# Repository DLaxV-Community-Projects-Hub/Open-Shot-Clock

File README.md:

# Open Shot Clock

Open Shot Clock is an Open Source and DIY Project aiming to minimize the barriers of entry for shot-clock-aided sports like Boxlacrosse and Sixes and maximizing the pure sports experience to an affordable price.

## Details

- 10" super bright LED digits (in color of your choice)
- indoor and outdoor usage
    - impact and water resistant portable design
    - LED brightness adjustable to your needs
- wireless and cable connection
- 12V input supply (portable battery or mains operation by AC-DC power supply)
- handheld controller
- wifi connection to smartphone
    - control option
    - settings change
    - firmware updates
- external horn for each display
- tripod stands ~2 meter height
- tested under competition conditions

The price tag is around 1000€ for materials and accessories. Depending on which design and battery options you choose, it might cost more.

For more information have a look at our [wiki](https://github.com/DLaxV-Community-Projects-Hub/Open-Shot-Clock/wiki/Open-Shot-Clock-Wiki) or this [blog](https://devdrik.de/blog/) made by [@devdrik](https://github.com/devdrik).

## The Open Shot Clock in Action

To see the Open Shot Clock in action check out the following recordings of Lacrosse high lights in Germany:

- [Men´s European Box Lacrosse Championship 2022 - Final: England vs. Germany](https://sportdeutschland.tv/germanylacrosse/european-box-lacrosse-championship-final-england-vs-germany) (face off at 0:07:20)
- [Women´s German Indoor Championchip 2023 - Final: HLC Rot-Weiss München vs. HTHC Hamburg A](https://sportdeutschland.tv/germanylacrosse/deutsche-indoor-lacrosse-meisterschaft-2023-finale) (draw at 0:07:35)
- [Men´s German Box Lacrosse Championchip 2023- Final: SG Süd vs. SC Frankfurt 1880](https://sportdeutschland.tv/germanylacrosse/deutsche-box-lacrosse-meisterschaft-2023-finale) (face off at 0:10:15)
- [Women´s German Indoor Championchip 2022 - Final: HLC Rot-Weiss München vs. HTHC Hamburg A](https://sportdeutschland.tv/germanylacrosse/finale-lacrosse-damen-indoor-meisterschaft-2022) (draw at 0:09:20)
- [Men´s German Box Lacrosse Championchip 2022- Final: Spreewölfe Berlin vs. KKHT SW Köln](https://sportdeutschland.tv/germanylacrosse/deutsche-meisterschaften-box-lacrosse-2022-spreewoelfe-berlin-vs-kkht-sw-koeln) (starting at Part 2)

## What´s Included Here

- Design Documentation for Open Shot Clock Displays and Controller
    - CAD and PCB designs
    - 3d printing files
    - DIY Building Instructions Manual (german)
    - BOM for Displays, Controller and accessories (german)
    - User Manual (german)
    - Source Code to run Displays and Controller
- Project Wiki (work in progress)

## Usage

To build your own Open Shot Clock you can find all documents/information in the [documentation](documentation/) folder.

### Getting All the Parts Needed

Please go through the BOM to make sure you have all parts needed available. In the BOM we have included recommendation links, where we recently purchased the parts. Be aware that you can choose from different design features which you have to cover in your purchases. The developement is stil ongoing so some design features are not yet tested or even sufficiently developed.

In the design 3d printing is requried. Make sure you print the necessary parts before starting to build or let them print by a printing service. Make sure the parts are printed with a heat and impact resistant 3d printing material. You can find recommended materials in the BOM.

For the PCBs you can use the design files to order them at a PCB manufacturer like [PCBWay](https://www.pcbway.com/) or you can get in touch with us, there are still some prototyping PCBs left of the current version. In the near future the PCB design has to be adapted to the new Heltec Lora 32 version 3.0. For now the new version is supported through a workaround. For more information check this [blog artical](https://devdrik.de/open-shot-clock-hannover/) from [@devdrik](https://github.com/devdrik).

### List of Optional Design Features:

- Displays - 19 mm thick highly machined base plate or 8 mm thick easy to build base plate
  - 19 mm makes a more stable design and is tested well
  - 8 mm base plate is much easier to build with less special machinery, but it´s not tested yet (there might be clashes with electronic parts inside the case)

- Displays - Temperature Managment (up to now we don´t know if a temperature management is necessary, to find out we integrated a temp sensor socket on the display pcbs, tests are still in planning)

  - No Cooling
  - Fan grids on the back for passiv cooling (default)
  - Active Fan with fan grids on the back (fan can be installed behind one fan grid and operated by one mosfet output, this feature is not yet included in the sourc code)

- Displays - Batteries (you can find different battery options in the BOM from which you can choose)
- Accessories - you can find different accessory options in the BOM from which you can choose
- Displays - Type-Plate customization (for having your own type-plate text you can get in touch with us, we can change the text for you)
- to be continued

### Assembling

When you have all parts available please follow the DIY Building Instructions Manual for assembling your Open Shot Clocks. Some parts like the base-, front- and back-plates or the aliminium extursion profiles need to be modified before they can be assembled. You can do the needed modification by using the drawings of these parts or you can get in touch with us, there are still some back plates left in our stock. In this [youtube playlist](https://www.youtube.com/watch?v=pQqHoa6__Ms&list=PLql27Iz3RF6tFwROZiCufJEf_9jadfyL8) you can see videos of [@devdrik](https://github.com/devdrik) performing the assembing process of an Open Shot Clock. In the future the playlist will be extended to cover all parts of the assembling process.

#### Heltec WiFi LoRa V2/V3

The V2 module is hard to get at the moment, so we added support for the new V3 version of the module, that is easy to source. To use V3 with PCBs designed for V2, you need to rewire some connections. So make sure not to use a V3 on a V2 PCB without modification!

What to do to use a V3 on a Display PCB v0.2:
- Do not connect GPIO21 and GPIO48 of the V3 to the display PCB
- Connect GPIO38 to the display PCB where GPIO21 would be
- Connect GPIO39 to the display PCB where GPIO48 would be
- In [config.h](code/display/include/config.h) set ```DISPLAY_PCB_VERSION V0_2_HACK```

What to do to use a V3 on a PCB for V2 (controller):
- Button BUTTON_PIN_B can not be used anymore
- Add pull-ups to all buttons (to be tested)

##### 5V Hack

Some Mosfet modules do not work with 3.3V on gate. To fix this on a v0.2 shotclock display PCB, we can disconnect the 3V3 pins from the of the heltec module and connect the corresponding pins on the display PCB to 5V of the heltec module.
This will bring all 3V3 on the display PCB to 5V, so be careful if you use a temperature sensor!

### How to Set Up the Firmware

You can find the source code for the controller and the displays in the code folder. Please just copy this repo to your VS Code with Plaformio extension and open both as projects. Fill in your preferred wifi credentials for setting up local device wifi networks to change settings. It is recommended to use different credentials for the controller and the displays to make sure you access the right devices settings.
Make sure to select the environment that fits the board you are using.

- flash controller
  - SPIFFS
  - source code
- flash displays
  - source code

## What´s Left to Do

- Tackle issues
- Build up Wiki with design insights, project history and roadmap
- Source code refactoring
- Design and test mdf display case as cost reduction opportunity
- pcb design to be ported to another open source platform and integration of heltc lora 32 v3.0 support
- Support first builders and gather feedback
- Offer english version of documents (if sufficiently demanded)
- to be continued

## How to Contribute

Feel free to customize your Open Shot Clock to your needs. For this purpose you can find the design files in the cad and pcb folders and the source code in the code folder. If you have ideas how to improve the Open Shot Clock and you need support for the integration or you want to share the benefits with the community please get in touch with us.

## Acknowledgement

Many thanks to [Ulf](https://github.com/ulf) for some initial inspiration in the approach to develop a LED shot clock. If you are looking out for a minimal and cheap setup for small indoor fields without obstacles have a look to [Ulf´s basketball shot clock tutotial](http://shotclock.de/)! With minor changes to the app it is possible to start with 30 seconds on the clock for lacrosse instead of 24 as for basketball. 

## Authors

- [@ChangeD20](https://github.com/ChangeD20)
- [@devdrik](https://github.com/devdrik)

## Contact

github@dlaxv.de

## License

[CERN OHL v2 Permissive](https://choosealicense.com/licenses/cern-ohl-p-2.0/)

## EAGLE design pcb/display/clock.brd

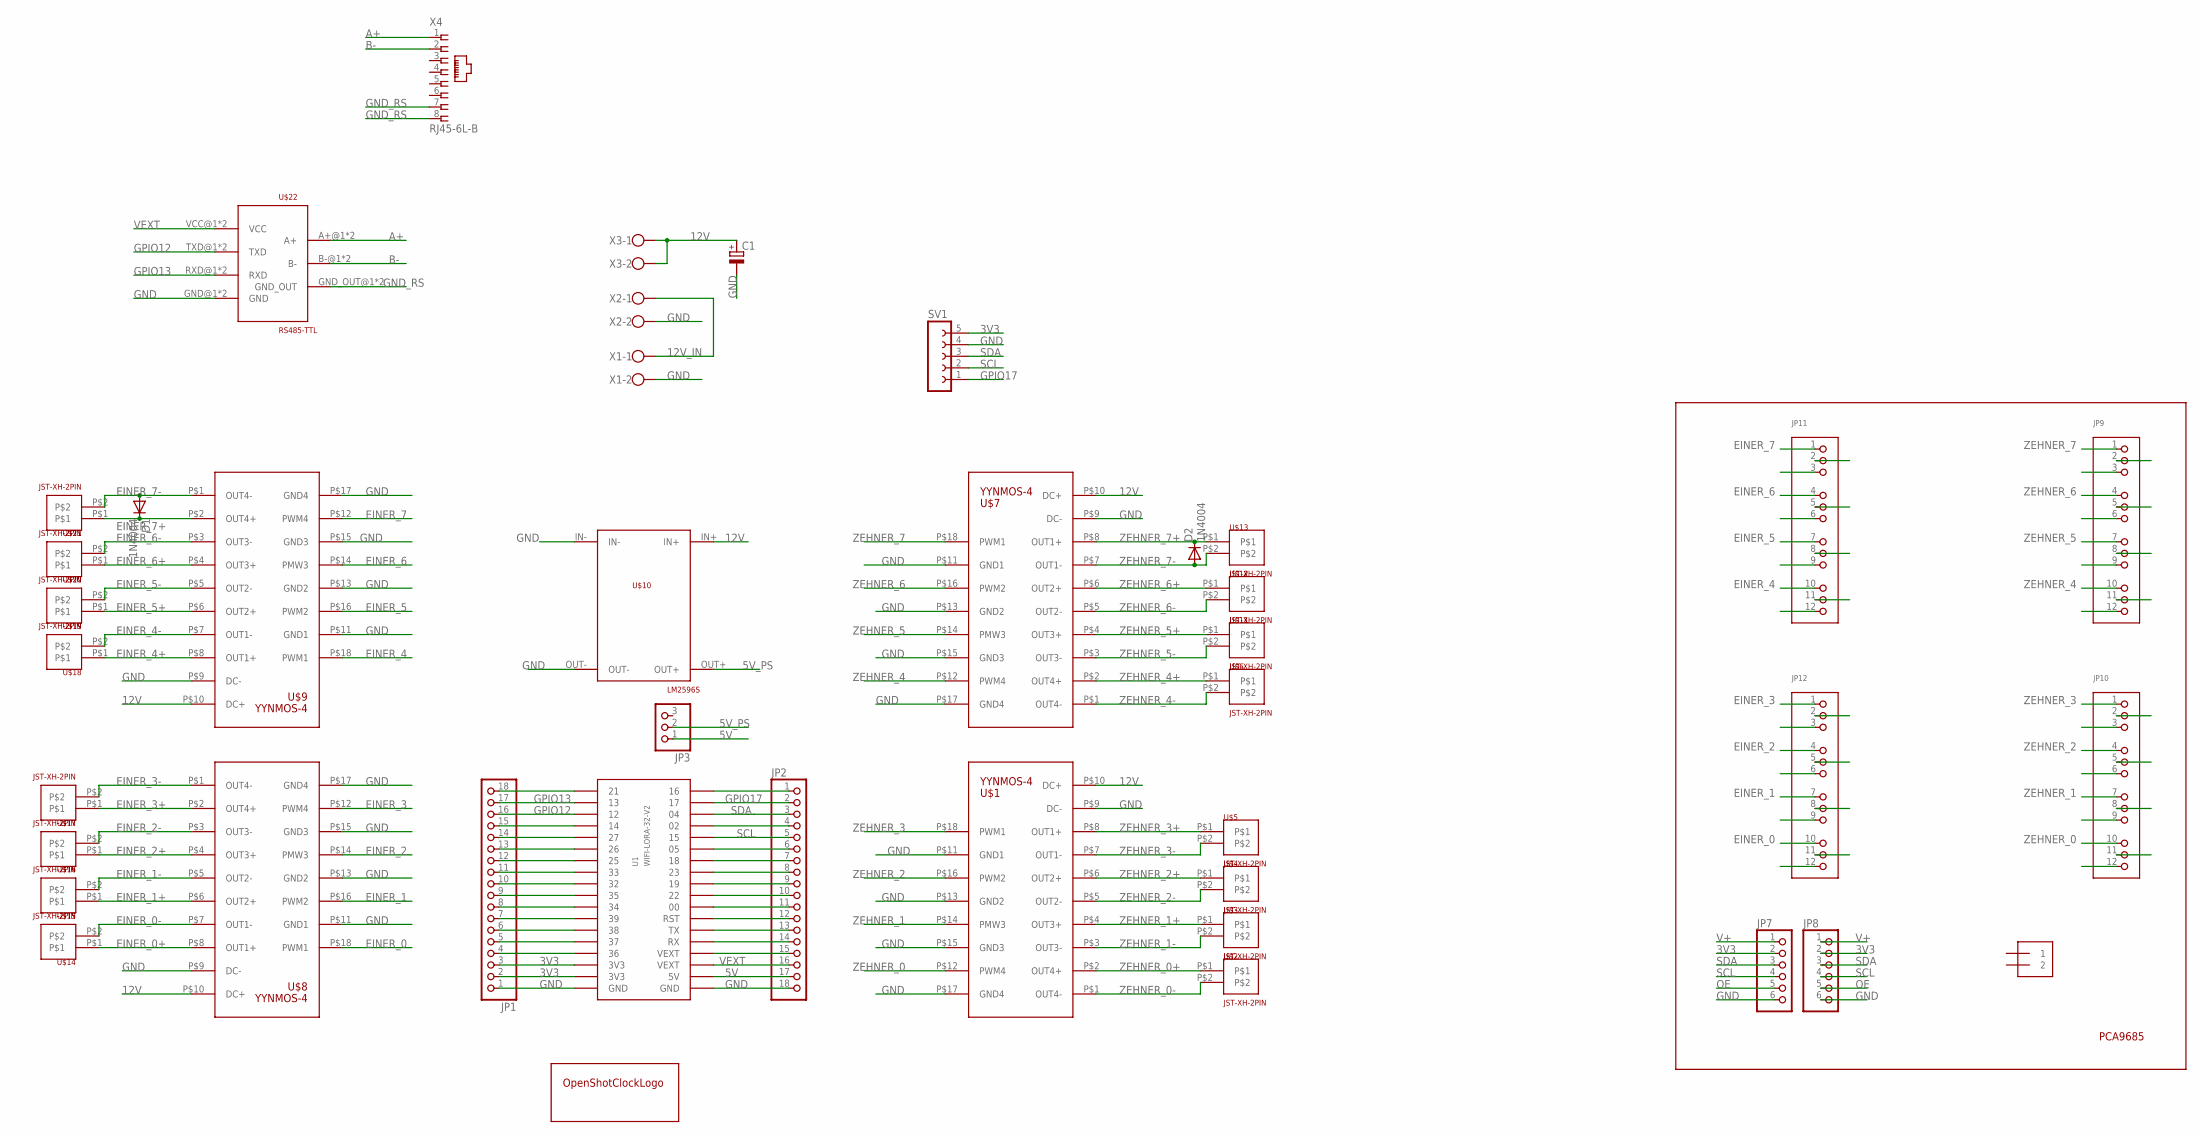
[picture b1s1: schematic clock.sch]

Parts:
C1: CPOL-EUE2.5-6; E2,5-6
D1, D2: 1N4004; DO41-10
J2: TERMBLOCK_1X2-3.5MM; 1X2-3.5MM
JP1, JP2: PINHD-1X18; 1X18
JP3: PINHD-1X3; 1X03
JP7, JP8: PINHD-1X6CB; 1X06-CLEANBIG
JP9, JP10, JP11, JP12: HEADER-3X04; 3X04
SV1: FE05-1
U1: WIFI-LORA-32-V2; 2.54MM_2X18
U$1, U$7, U$8, U$9: YYNMOS-4
U$2, U$3, U$4, U$5, U$6, U$11, U$12, U$13, U$14, U$15, U$16, U$17, U$18, U$19, U$20, U$21: JST-XH-2PIN
U$10: LM2596S
U$22: RS485-TTL
U$23: OPEN-SHOT-CLOCK-LOGO
X1, X2, X3: W237-102
X4: RJ45-6L-B; RJ45-NO-SHIELD

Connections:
3V3: JP1.2, JP1.3, JP7.2, JP8.2, SV1.5, U1.P$34 (3V3), U1.P$35 (3V3)
5V: JP2.17, JP3.1, U1.P$2 (5V)
5V_PS: JP3.2, U$10.OUT+
12V: C1.+, U$1.P$10 (DC+), U$7.P$10 (DC+), U$8.P$10 (DC+), U$9.P$10 (DC+), U$10.IN+, X3.1, X3.2
12V_IN: X1.1, X2.1
A+: U$22.A+@1 (A+), U$22.A+@2 (A+), X4.1
B-: U$22.B-@1 (B-), U$22.B-@2 (B-), X4.2
EINER_0: JP12.10, U$8.P$18 (PWM1)
EINER_0+: U$8.P$8 (OUT1+), U$14.P$1
EINER_0-: U$8.P$7 (OUT1-), U$14.P$2
EINER_1: JP12.7, U$8.P$16 (PWM2)
EINER_1+: U$8.P$6 (OUT2+), U$15.P$1
EINER_1-: U$8.P$5 (OUT2-), U$15.P$2
EINER_2: JP12.4, U$8.P$14 (PMW3)
EINER_2+: U$8.P$4 (OUT3+), U$16.P$1
EINER_2-: U$8.P$3 (OUT3-), U$16.P$2
EINER_3: JP12.1, U$8.P$12 (PWM4)
EINER_3+: U$8.P$2 (OUT4+), U$17.P$1
EINER_3-: U$8.P$1 (OUT4-), U$17.P$2
EINER_4: JP11.10, U$9.P$18 (PWM1)
EINER_4+: U$9.P$8 (OUT1+), U$18.P$1
EINER_4-: U$9.P$7 (OUT1-), U$18.P$2
EINER_5: JP11.7, U$9.P$16 (PWM2)
EINER_5+: U$9.P$6 (OUT2+), U$19.P$1
EINER_5-: U$9.P$5 (OUT2-), U$19.P$2
EINER_6: JP11.4, U$9.P$14 (PMW3)
EINER_6+: U$9.P$4 (OUT3+), U$20.P$1
EINER_6-: U$9.P$3 (OUT3-), U$20.P$2
EINER_7: JP11.1, U$9.P$12 (PWM4)
EINER_7+: D1.C, U$9.P$2 (OUT4+), U$21.P$1
EINER_7-: D1.A, U$9.P$1 (OUT4-), U$21.P$2
GND: C1.-, JP1.1, JP2.18, JP7.6, JP8.6, SV1.4, U1.P$1 (GND), U1.P$36 (GND), U$1.P$9 (DC-), U$1.P$11 (GND1), U$1.P$13 (GND2), U$1.P$15 (GND3), U$1.P$17 (GND4), U$7.P$9 (DC-), U$7.P$11 (GND1), U$7.P$13 (GND2), U$7.P$15 (GND3), U$7.P$17 (GND4), U$8.P$9 (DC-), U$8.P$11 (GND1), U$8.P$13 (GND2), U$8.P$15 (GND3), U$8.P$17 (GND4), U$9.P$9 (DC-), U$9.P$11 (GND1), U$9.P$13 (GND2), U$9.P$15 (GND3), U$9.P$17 (GND4), U$10.IN-, U$10.OUT-, U$22.GND@1 (GND), U$22.GND@2 (GND), X1.2, X2.2
GND_RS: U$22.GND_OUT@1 (GND_OUT), U$22.GND_OUT@2 (GND_OUT), X4.7, X4.8
GPIO12: JP1.16, U1.P$21 (12), U$22.TXD@1 (TXD), U$22.TXD@2 (TXD)
GPIO13: JP1.17, U1.P$20 (13), U$22.RXD@1 (RXD), U$22.RXD@2 (RXD)
GPIO17: JP2.2, SV1.1, U1.P$17 (17)
unnamed: JP1.18, U1.P$19 (21)
unnamed: JP1.15, U1.P$22 (14)
unnamed: JP1.14, U1.P$23 (27)
unnamed: JP1.13, U1.P$24 (26)
unnamed: JP1.12, U1.P$25 (25)
unnamed: JP1.11, U1.P$26 (33)
unnamed: JP1.10, U1.P$27 (32)
unnamed: JP1.9, U1.P$28 (35)
unnamed: JP1.8, U1.P$29 (34)
unnamed: JP1.7, U1.P$30 (39)
unnamed: JP1.6, U1.P$31 (38)
unnamed: JP1.5, U1.P$32 (37)
unnamed: JP1.4, U1.P$33 (36)
unnamed: JP2.1, U1.P$18 (16)
unnamed: JP2.4, U1.P$15 (02)
unnamed: JP2.6, U1.P$13 (05)
unnamed: JP2.7, U1.P$12 (18)
unnamed: JP2.8, U1.P$11 (23)
unnamed: JP2.9, U1.P$10 (19)
unnamed: JP2.10, U1.P$9 (22)
unnamed: JP2.11, U1.P$8 (00)
unnamed: JP2.12, U1.P$7 (RST)
unnamed: JP2.13, U1.P$6 (TX)
unnamed: JP2.14, U1.P$5 (RX)
unnamed: JP2.15, U1.P$4 (VEXT)
OE: JP7.5, JP8.5
SCL: JP2.5, JP7.4, JP8.4, SV1.2, U1.P$14 (15)
SDA: JP2.3, JP7.3, JP8.3, SV1.3, U1.P$16 (04)
V+: JP7.1, JP8.1
VEXT: JP2.16, U1.P$3 (VEXT), U$22.VCC@1 (VCC), U$22.VCC@2 (VCC)
ZEHNER_0: JP10.10, U$1.P$12 (PWM4)
ZEHNER_0+: U$1.P$2 (OUT4+), U$2.P$1
ZEHNER_0-: U$1.P$1 (OUT4-), U$2.P$2
ZEHNER_1: JP10.7, U$1.P$14 (PMW3)
ZEHNER_1+: U$1.P$4 (OUT3+), U$3.P$1
ZEHNER_1-: U$1.P$3 (OUT3-), U$3.P$2
ZEHNER_2: JP10.4, U$1.P$16 (PWM2)
ZEHNER_2+: U$1.P$6 (OUT2+), U$4.P$1
ZEHNER_2-: U$1.P$5 (OUT2-), U$4.P$2
ZEHNER_3: JP10.1, U$1.P$18 (PWM1)
ZEHNER_3+: U$1.P$8 (OUT1+), U$5.P$1
ZEHNER_3-: U$1.P$7 (OUT1-), U$5.P$2
ZEHNER_4: JP9.10, U$7.P$12 (PWM4)
ZEHNER_4+: U$6.P$1, U$7.P$2 (OUT4+)
ZEHNER_4-: U$6.P$2, U$7.P$1 (OUT4-)
ZEHNER_5: JP9.7, U$7.P$14 (PMW3)
ZEHNER_5+: U$7.P$4 (OUT3+), U$11.P$1
ZEHNER_5-: U$7.P$3 (OUT3-), U$11.P$2
ZEHNER_6: JP9.4, U$7.P$16 (PWM2)
ZEHNER_6+: U$7.P$6 (OUT2+), U$12.P$1
ZEHNER_6-: U$7.P$5 (OUT2-), U$12.P$2
ZEHNER_7: JP9.1, U$7.P$18 (PWM1)
ZEHNER_7+: D2.C, U$7.P$8 (OUT1+), U$13.P$1
ZEHNER_7-: D2.A, U$7.P$7 (OUT1-), U$13.P$2

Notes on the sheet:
PCA9685

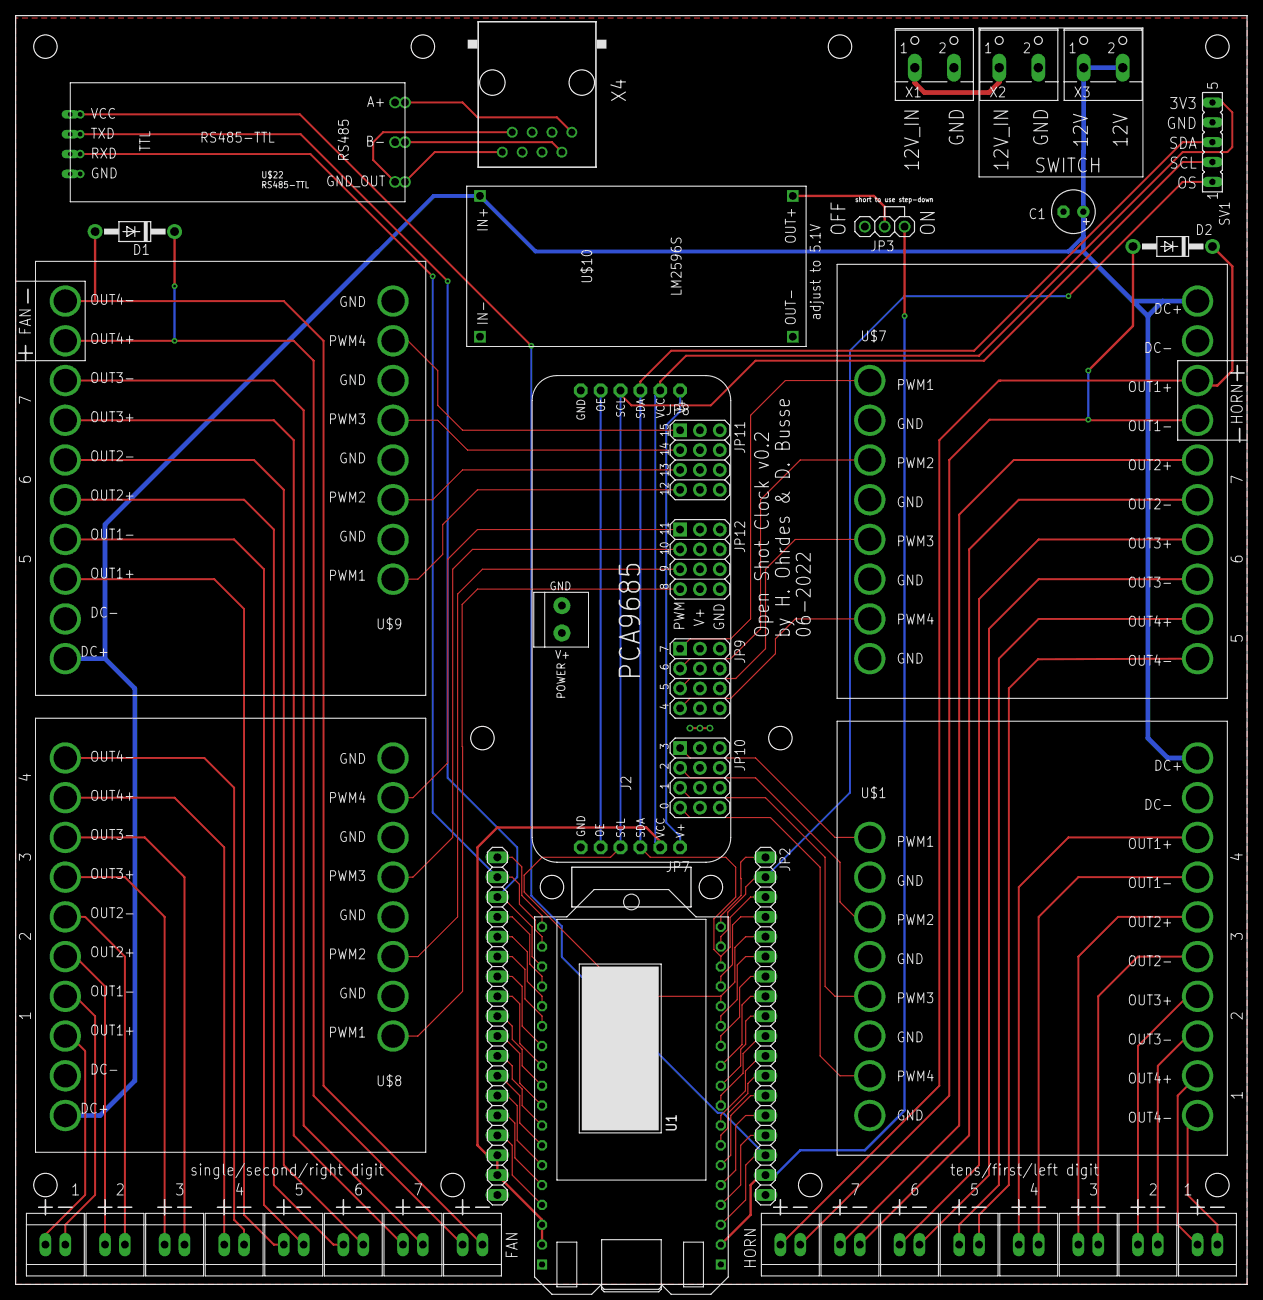
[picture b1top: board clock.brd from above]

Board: 2 copper layers, 157.5 x 162.2 mm, 42 parts (1 on the bottom side), 90 nets.

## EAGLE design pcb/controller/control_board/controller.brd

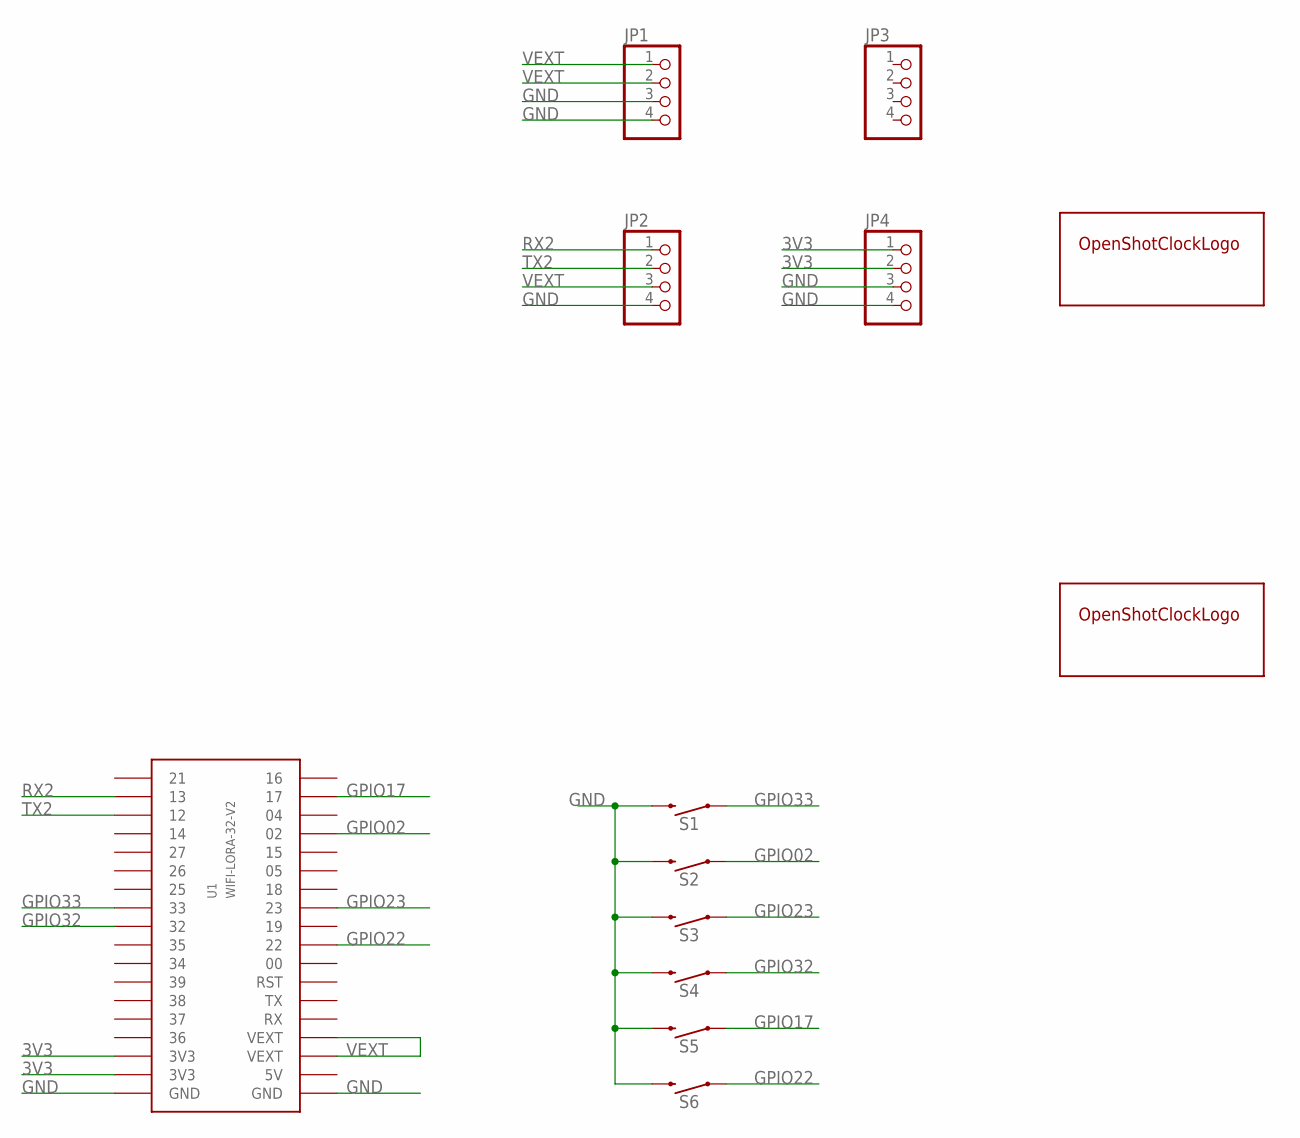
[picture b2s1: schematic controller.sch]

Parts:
JP1, JP2, JP3, JP4: PINHD-1X4; 1X04
S1, S2, S3, S4, S5, S6: MOMENTARY-SWITCH-SPST-SMD-6.0X3.5MM; TACTILE_SWITCH_SMD_6.0X3.5MM
U1: WIFI-LORA-32-V2; 2.54MM_2X18
U$2, U$5: OPEN-SHOT-CLOCK-LOGOOSCL-SMALL; OPEN-SHOT-CLOCK-LOGO-SMALL

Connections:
3V3: JP4.1, JP4.2, U1.P$34 (3V3), U1.P$35 (3V3)
GND: JP1.3, JP1.4, JP2.4, JP4.3, JP4.4, S1.2, S2.2, S3.2, S4.2, S5.2, S6.2, U1.P$1 (GND), U1.P$36 (GND)
GPIO02: S2.1, U1.P$15 (02)
GPIO17: S5.1, U1.P$17 (17)
GPIO22: S6.1, U1.P$9 (22)
GPIO23: S3.1, U1.P$11 (23)
GPIO32: S4.1, U1.P$27 (32)
GPIO33: S1.1, U1.P$26 (33)
RX2: JP2.1, U1.P$20 (13)
TX2: JP2.2, U1.P$21 (12)
VEXT: JP1.1, JP1.2, JP2.3, U1.P$3 (VEXT), U1.P$4 (VEXT)

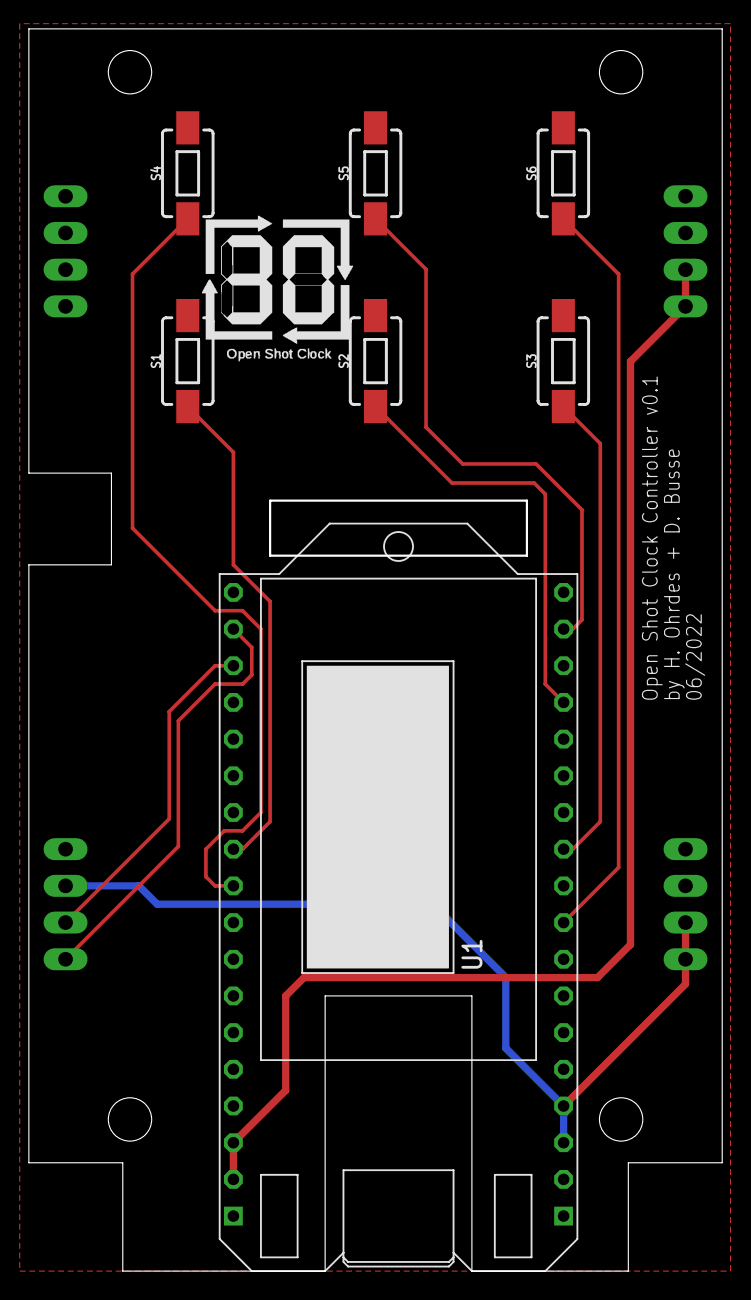
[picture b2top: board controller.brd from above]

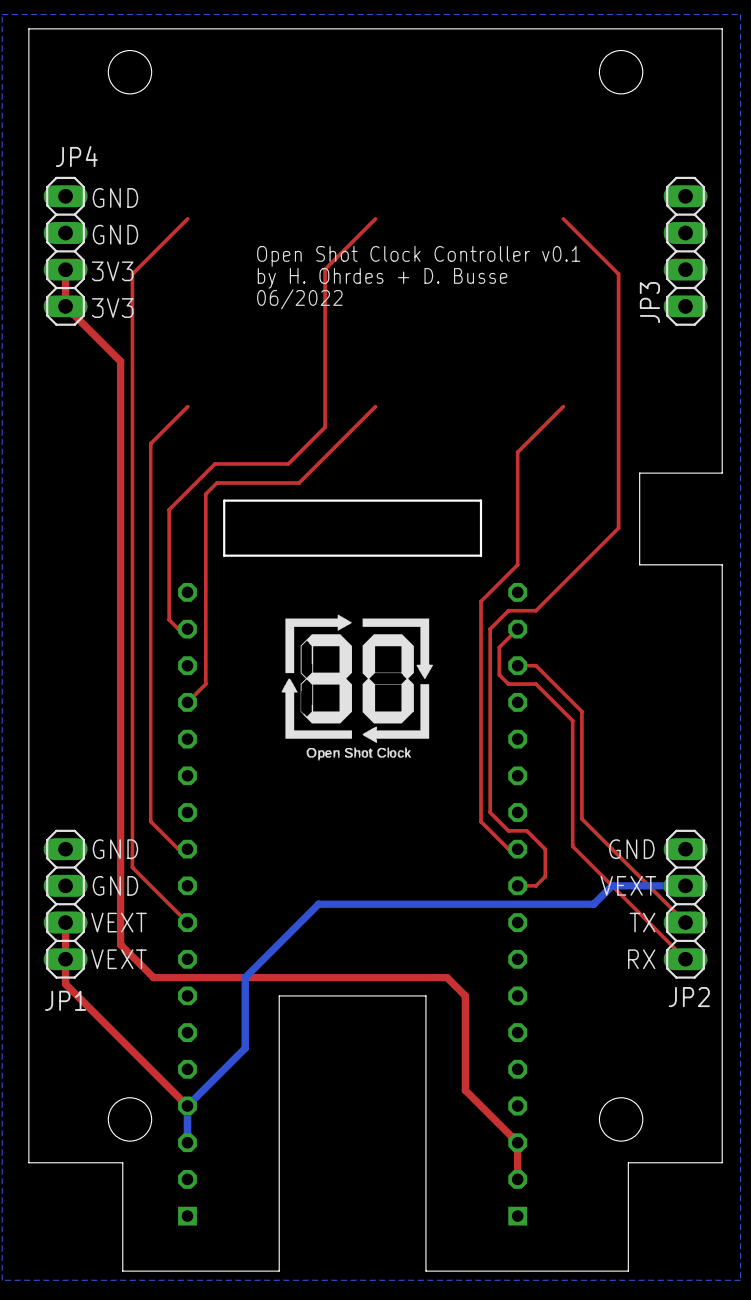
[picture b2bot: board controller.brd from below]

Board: 2 copper layers, 48.0 x 86.0 mm, 13 parts (5 on the bottom side), 11 nets.

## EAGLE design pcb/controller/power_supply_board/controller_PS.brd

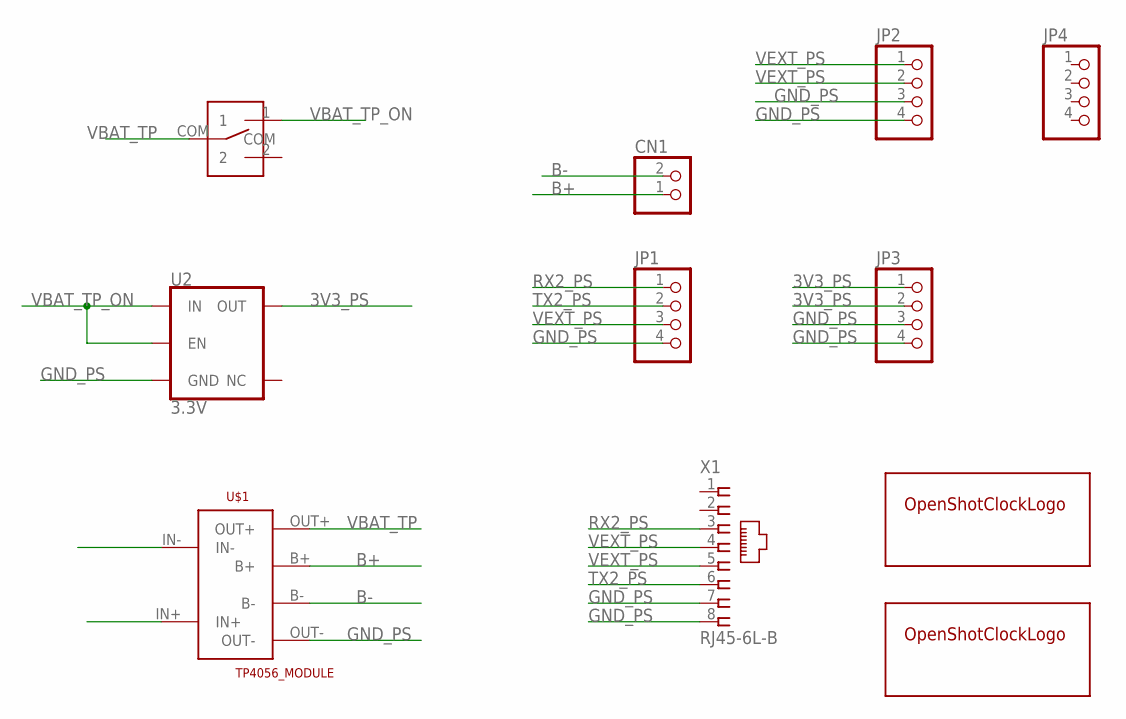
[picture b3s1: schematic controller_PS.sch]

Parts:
CN1: JST_2PIN-THM-RA; JST-PH-2-THM-RA
JP1, JP2, JP3, JP4: PINHD-1X4; 1X04
U2: 3.3V; SOT23-5
U$1: TP4056_MODULE
U$3, U$4: OPEN-SHOT-CLOCK-LOGOOSCL-SMALL; OPEN-SHOT-CLOCK-LOGO-SMALL
U$6: SK12D07VG4
X1: RJ45-6L-B; RJ45-NO-SHIELD

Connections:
3V3_PS: JP3.1, JP3.2, U2.5 (OUT)
B+: CN1.1 (2), U$1.B+
B-: CN1.2 (1), U$1.B-
GND_PS: JP1.4, JP2.3, JP2.4, JP3.3, JP3.4, U2.2 (GND), U$1.OUT-, X1.7, X1.8
RX2_PS: JP1.1, X1.3
TX2_PS: JP1.2, X1.6
VBAT_TP: U$1.OUT+, U$6.COM
VBAT_TP_ON: U2.1 (IN), U2.3 (EN), U$6.1
VEXT_PS: JP1.3, JP2.1, JP2.2, X1.4, X1.5

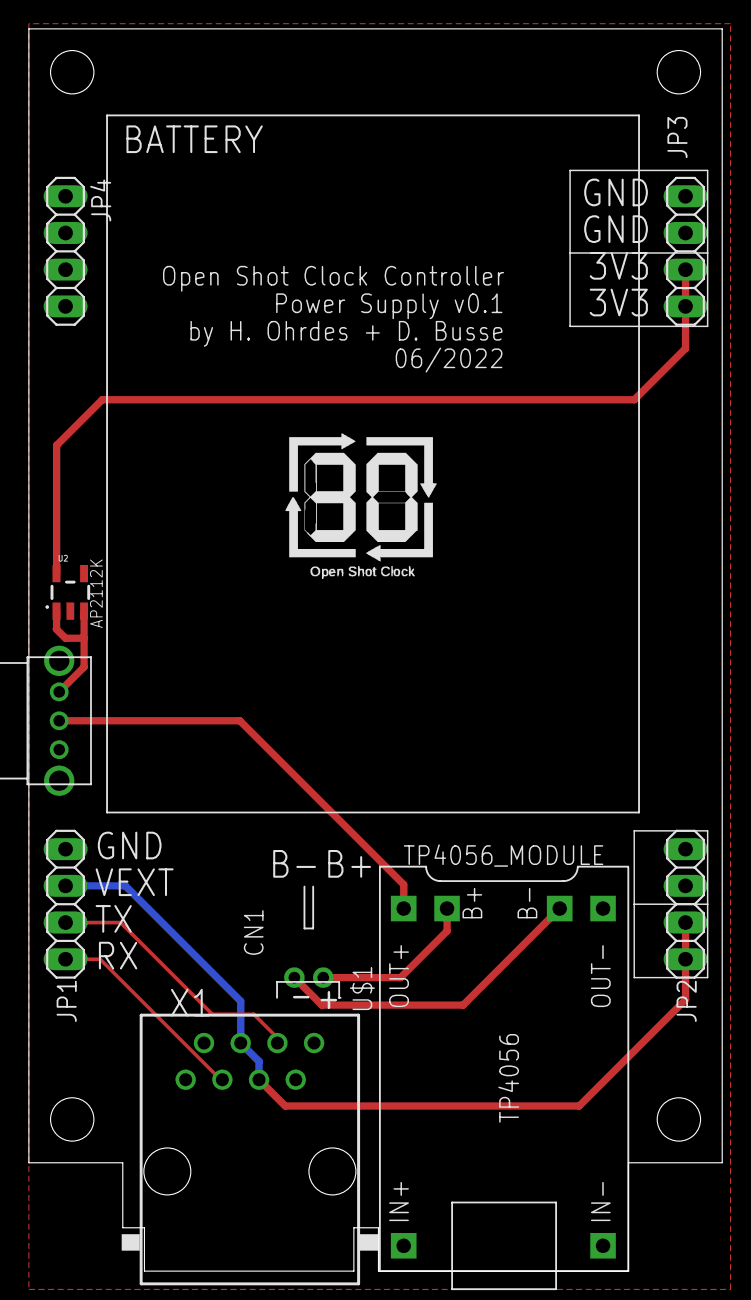
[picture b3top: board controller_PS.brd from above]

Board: 2 copper layers, 48.0 x 86.0 mm, 11 parts (1 on the bottom side), 9 nets.

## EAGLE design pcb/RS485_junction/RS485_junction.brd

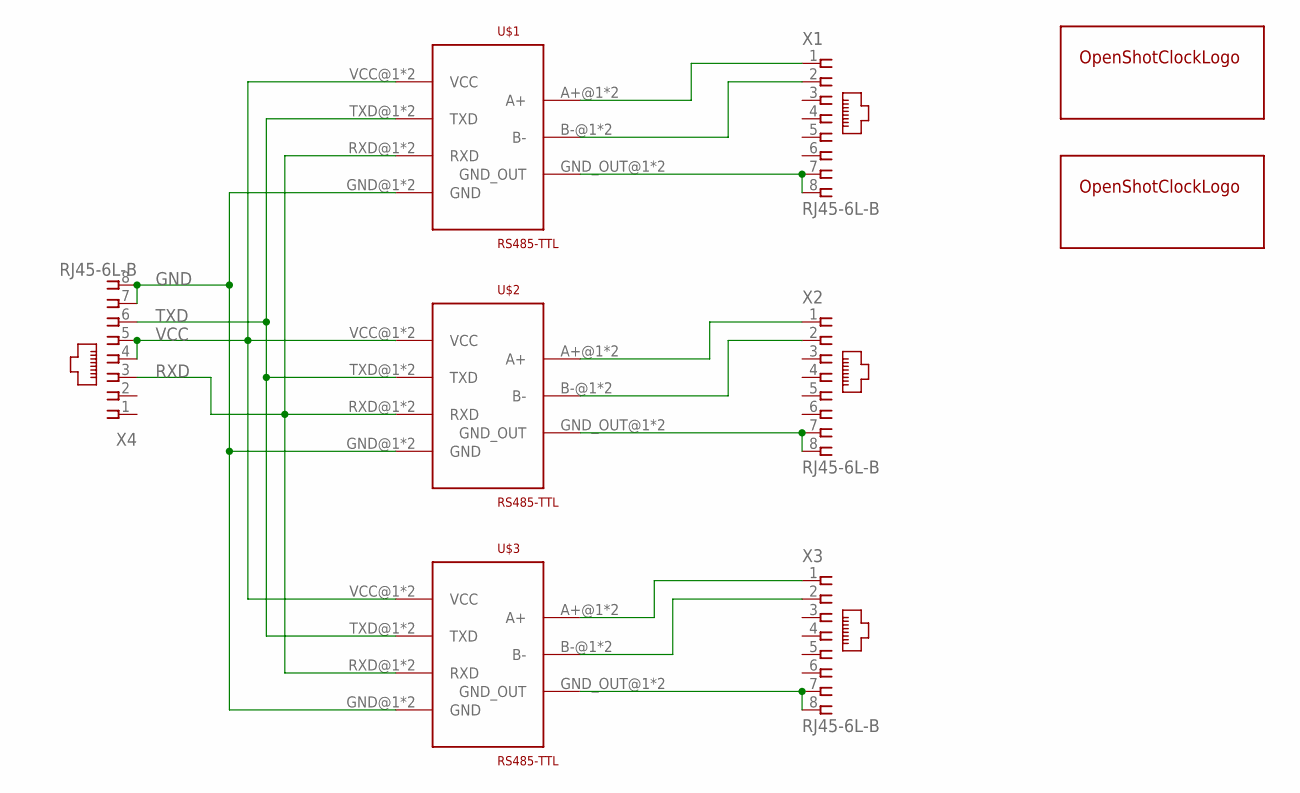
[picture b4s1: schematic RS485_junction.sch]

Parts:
U$1, U$2, U$3: RS485-TTL
U$4: OPEN-SHOT-CLOCK-LOGOOSCL-SMALL; OPEN-SHOT-CLOCK-LOGO-SMALL
U$5: OPEN-SHOT-CLOCK-LOGOOSCL-H50MM; OPEN-SHOT-CLOCK-LOGO-H50MM
X1, X2, X3, X4: RJ45-6L-B; RJ45-NO-SHIELD

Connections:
GND: U$1.GND@1 (GND), U$1.GND@2 (GND), U$2.GND@1 (GND), U$2.GND@2 (GND), U$3.GND@1 (GND), U$3.GND@2 (GND), X4.7, X4.8
unnamed: U$1.A+@1 (A+), U$1.A+@2 (A+), X1.1
unnamed: U$1.B-@1 (B-), U$1.B-@2 (B-), X1.2
unnamed: U$1.GND_OUT@1 (GND_OUT), U$1.GND_OUT@2 (GND_OUT), X1.7, X1.8
unnamed: U$2.A+@1 (A+), U$2.A+@2 (A+), X2.1
unnamed: U$2.B-@1 (B-), U$2.B-@2 (B-), X2.2
unnamed: U$2.GND_OUT@1 (GND_OUT), U$2.GND_OUT@2 (GND_OUT), X2.7, X2.8
unnamed: U$3.GND_OUT@1 (GND_OUT), U$3.GND_OUT@2 (GND_OUT), X3.7, X3.8
unnamed: U$3.A+@1 (A+), U$3.A+@2 (A+), X3.1
unnamed: U$3.B-@1 (B-), U$3.B-@2 (B-), X3.2
RXD: U$1.RXD@1 (RXD), U$1.RXD@2 (RXD), U$2.RXD@1 (RXD), U$2.RXD@2 (RXD), U$3.RXD@1 (RXD), U$3.RXD@2 (RXD), X4.3
TXD: U$1.TXD@1 (TXD), U$1.TXD@2 (TXD), U$2.TXD@1 (TXD), U$2.TXD@2 (TXD), U$3.TXD@1 (TXD), U$3.TXD@2 (TXD), X4.6
VCC: U$1.VCC@1 (VCC), U$1.VCC@2 (VCC), U$2.VCC@1 (VCC), U$2.VCC@2 (VCC), U$3.VCC@1 (VCC), U$3.VCC@2 (VCC), X4.4, X4.5

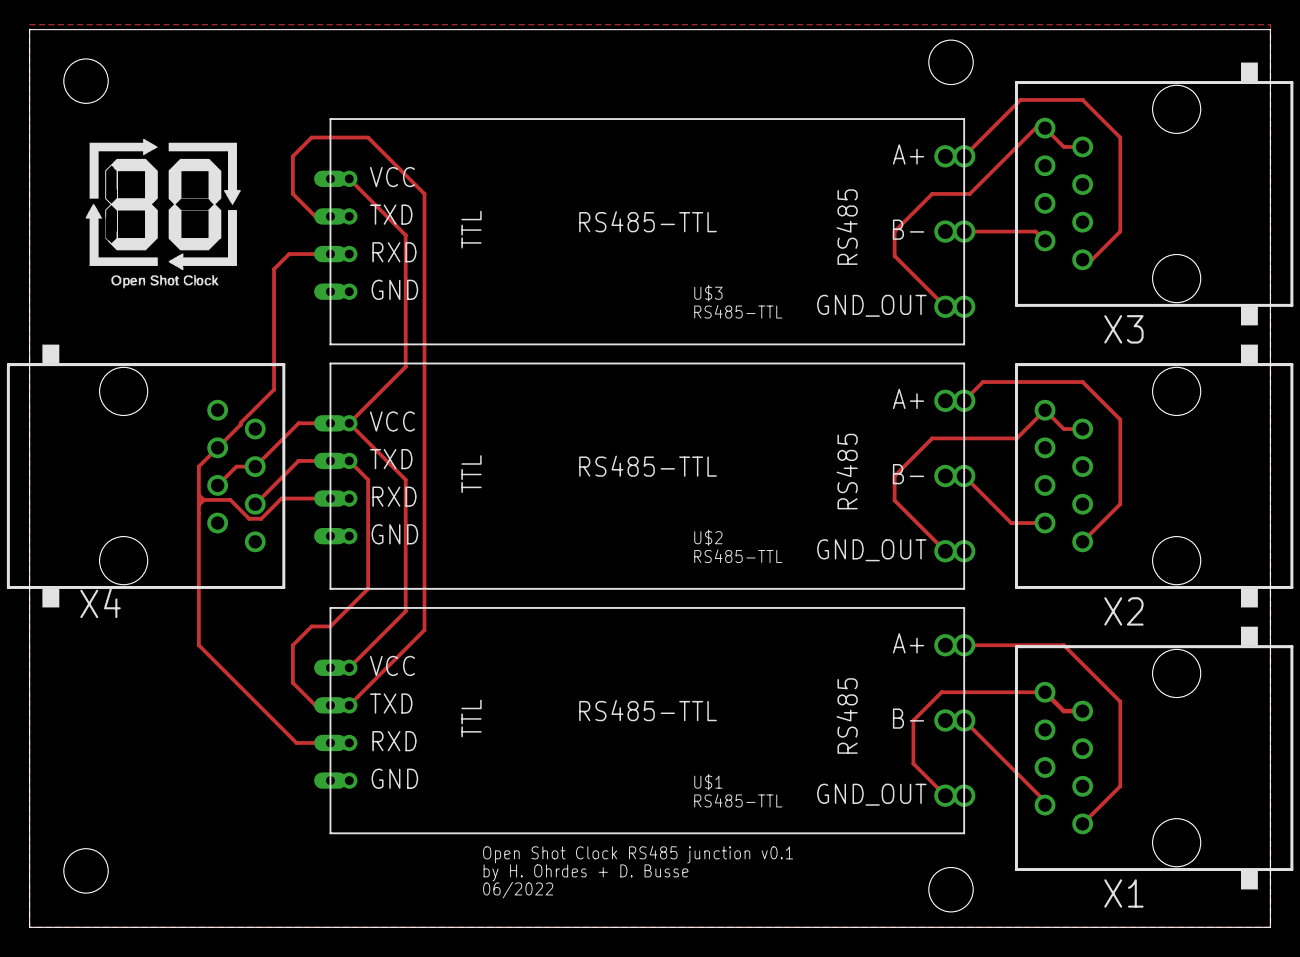
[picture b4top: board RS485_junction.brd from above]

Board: 2 copper layers, 83.8 x 60.6 mm, 9 parts (1 on the bottom side), 13 nets.

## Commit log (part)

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2021-08-31 Ordner mit Temp_Monitor_Version hinzugefügt
2021-09-13 sender aktualisiert - starte Bereinigung
2021-09-13 Aufgeräumt-OTA-OLED_Display_Update-Kanal_Wahl_Web_Server-Temp_Sensor_raus
2021-09-27 Function_display-Display_aus_wenn_Smartphone_Steuerung
2021-09-27 3_sec_Press_Reset_with_Stop
2021-10-15 Display aus wenn Steuerung per Smartphone bug fix
2021-12-14 port to VS code
2021-12-15 updated_design_on_channel_selection_sender_and_receiver
2021-12-15 updated_design_on_channel_selection_sender_and_receiver (#3)
2022-01-21 Set tx power to 9 - test positiv (#4)
2022-01-21 added settings page with brightness control
2022-01-21 deleted not needed variables
2022-02-08 styled settings page and select element
2022-02-09 again
2022-02-09 updated sender button pin-out/wifi new controller
2022-03-25 unwantedRecs
2022-03-25 Integrated 3 versions
2022-03-25 fixed send command
2022-03-29 added console info when fan starts/stops
2022-03-29 Test positiv - both
2022-04-13 Button_Layout_Changeed_to_Controller_V2.1
2022-05-14 added_Hannover_Clock_to_Wifi_Options
2022-06-03 corrected pin out discription reset and cancel
2022-06-03 integratedt serial2 for rs485 test
2022-06-14 positiv rs485 test
2022-07-27 added 2 Buttons, minor refactoring
2022-07-27 added DS_Store to gitignore
2022-07-27 updated async webserver to fix bug with current esp tools
2022-09-30 implement rs 485 communication (#22)
    * Initial base (#2)
    * initial commit
    * Ordner mit Temp_Monitor_Version hinzugefügt
    * sender aktualisiert - starte Bereinigung
    * Aufgeräumt-OTA-OLED_Display_Update-Kanal_Wahl_Web_Server-Temp_Sensor_raus
    * sender_OTA_und_Kanalwahl-Display_OLED_Design_und_Connecting_Funktion
2022-12-23 renamed Sender/Receiver to Controller/Display
2023-01-02 added pcb files
2023-01-02 refactores folder structure
2023-01-02 added logo to assets
2023-01-02 Update README.md
    added Usage
2023-02-17 Add files via upload
    updated some costs and links
    changed ethernet socket product
2023-03-31 Add files via upload
    added new named images again
2023-03-31 Update README.md
    changed image naming from *.svg to *.pptx.svg
2023-03-31 Create README.md
    added design option 8 mm thick base plate
2023-03-31 Add files via upload
    added mark for 5 mm drilling hole (antenna)
2023-03-31 Add files via upload
    - added 8 mm base plate option flange design parts
    - updated tripod flange design to solve issue #23
    - added horn cuff clip to solve issue #23
2023-03-31 Update README.md
    typo
2023-04-04 swithed webserver dependency to use HTTPS instead of SSH
2023-04-05 Update README.md
    changed to assets readme.md
2023-04-05 deleted unnecessary files
2023-04-05 Update README.md
    changed theme image link to new assets branch
2023-04-05 updated theme with 3d-printing corner joint
2023-04-05 updated cad and documentation files
2023-04-06 updated sourcing-list and instructions
2023-04-06 Dev (#32)
    * manually merged refactoring branch (issue 6)
    * swithed webserver dependency to use HTTPS instead of SSH
    * swithed webserver dependency to use HTTPS instead of SSH
    * deleted assets folder and changed config
    * Update README.md
    changed theme image link to new assets branch
2023-10-02 initial test
2023-10-20 switched to RadioLib to be able to use heltec v3. Added heltec_wifi_lora_32_V3 env. Added v3 pin configs. Still WIP
2023-10-20 switched to RadioLib to be able to use heltec v3. Added heltec_wifi_lora_32_V3 env. Added v3 pin configs. For display. Still WIP
2023-11-02 added V3 infos to README
2023-11-02 minor cleaning
2023-11-02 refactored controller platformio.ini
2023-11-06 added I2C handling for different boards. Added PCB config to choose PCB
2023-11-06 cleanup
2023-11-06 removed twowire object for V2 when used with OLED_I2C, bc didn't work
2024-01-03 added v3 mod image to readme
2024-01-05 added 5V mod
2024-01-25 added dewarp files for abs/asa prints
2024-02-12 refactored pin and board config
2024-02-23 added higher controller
2024-03-04 added option to reset to different times, refactored button handling
2024-03-10 added reset on conntecion lost
2024-03-10 changed wifi name for display
2024-03-11 changed channels to use syncword instead of band
2024-03-11 changed config, removed ESP.restart
2024-03-11 changed channel to use syncword for controller + refactoring
2024-03-12 config cleanup
2024-03-12 removed prints
2024-03-13 fixed platform version
2024-03-17 added frequency to channel, so it uses different frequency and sync words
2024-04-13 Feature/make channels work (#37)
    * added frequency to channel, so it uses different frequency and sync words
    * added channel to message, added message validation
2024-05-17 fixed crashing display (lora restart on fail), fixed OLED mode display
2024-05-21 added versions page for display
2024-05-22 added versions for controller
2024-05-22 17 displays and controller firmware version not visible (#48)
    * added versions page for display
    * added versions for controller
2024-05-22 fixed bug, brightnesslevel now using exact string position from message
2024-05-25 config?
2024-05-30 fixed bug for RS485 communication (there is an extra whitespace sent, that crashed validation)
2024-05-30 junction v1.1 PCB in kicad (#52)
2024-05-30 added controller v2.1 in kicad
2024-05-31 changed extra holes in junction to be THT to make them manufacturable
2024-06-13 added controller V2.1
2024-06-13 fixed wrong pcb version error
2024-08-08 fixed controller by updating lib_deps / added build_flag for async webserver async-mode / updated main for ElegantOTA
2024-08-18 further Tests on receive delay - 1 sec plus delay without peripheral - little delay with peripheral
2024-11-17 Final Version of Prototype Rev. 00
    Switched back to PCA9685 for PWM, removed high side switch
    Updated some component values
2024-12-09 add new controller and junction case, add looser horn cuff model
2025-02-15 Final Version of new Controller Rev. 00 (Prototype)
2025-02-15 Add BOM files and adjust gitignore to not exclude BOMs
2025-02-17 Added support for new custom display hardware
    Removed Heltec library
    Implemented OLED display using Adafruit library
    Increased RadioLib version as bugs for LLCC68 where fixed
2025-02-19 prevent resetTime to be over 99 or unter 0
2025-02-19 refactor: rename vars, remove vars, stop turning off display on wifi control, bc it works
2025-02-19 refactoring: renaming, sorting
2025-02-20 refactor count function and variable names
2025-02-20 refactor: moving functions
2025-02-20 refactor: rename button variables and state for consistency
2025-02-20 Chore/refactor button handling (#55)
2025-02-20 Prepare release v1.2.0 (#56)
    - add heltec v3 compatibility
    - add version endpoint
    - add new controller PCB using kicad
    - update junction PCB using kicad
    - change lora communication, new channel system
    - cad updates, new controller, junction case, horn cuff, anti-warp corners
2025-02-21 feat: add git tag information to versioning in display and controller modules
2025-02-21 Prepare release v1.2.1 (#57)
    * feat: add git tag information to versioning in display and controller modules
2025-02-23 Added ReleaseNotes for Display
    Deleted old files
2025-03-30 Revision 01 of Controller hardware
    - fixed bugs from revision 00
    - changed folder structure
    - added ReleaseNotes_Controller.md to keep track of changes
2025-04-08 Display HW Revision 01
2025-04-09 Final adjustments and BOM optimization
2025-04-11 Update wrong values after import in JLC for production
2025-05-03 Update component values after feedback from JLC
2025-05-11 Updated ReleaseNotes_Controller.md with know issues of R01
    Changed SMD button JLC order number to version without mounting holes
2025-05-11 WIP for R00/R01 hardware
2025-07-20 Add missing osc_logo.h header file
    Set library dependencies to fixed versions
2025-07-20 Added Vext to config
    Manually integrated changes for HW R0/R1
2025-07-30 feat: add honk function for simultaneous B4 and B5 presses
2025-07-30 feat: update honking functionality and clean up button handling
2025-08-23 feat: add toggleResetTime function on extra long press on BTN_3
2025-08-23 refactor: remove debug prints from toggleResetTime function
2025-08-24 Prepare release v1.3.0 (#59)
    * manually merged refactoring branch (issue 6)
    * swithed webserver dependency to use HTTPS instead of SSH
    * swithed webserver dependency to use HTTPS instead of SSH
    * deleted assets folder and changed config
    * Update README.md
    changed theme image link to new assets branch
2025-09-05 Changes for Heltec V3
2025-09-05 Updated ReleaseNotes_Controller
2025-09-06 update controller PCB: wider traces, fix missing trace on V+, add comments, update gerber files (#60)
2025-09-16 controller v3.0 cad design and print files added initially
2025-10-10 feat: add honk volume control to settings and update server handling
2025-10-10 feat: implement channel selection dropdown and update server handling for channel changes
2025-10-10 feat: add start time selection to settings and update server handling for start time changes
2025-10-10 style: enhance settings page layout and improve button aesthetics and mobile use
2025-10-11 fix: update volume and tick mappings for horn and LEDs for improved functionality
2025-11-30 Conerted to KiCad 9 file version.
2026-03-01 add fan grid with screws and seal and led spacers
2026-03-02 Adjusted footprint of mosfets for 0.15mm solder mask spacing
    New Gerber files
2026-03-10 Exclude Symbols from BOM
2026-04-03 added R2 pin config
2026-04-03 pinned ElegantOTA version to omit build error
2026-04-03 init SPI corretly, fix PWM_OE pin, add debug logs
2026-04-28 Feat/honk volume control (#61)
    * feat: add honk volume control and move honking logic to controller
    * feat: add honk volume control to settings and update server handling
    * feat: implement channel selection dropdown and update server handling for channel changes
    * style: update settings page design for improved aesthetics and usability
    * feat: add start time selection to settings and update server handling for start time changes
    * style: enhance settings page layout and improve button aesthetics and mobile use
2026-04-28 FIX: potential race condition with LoRa RX flag beeing reset after handling message.
    When a message is received during the processing of the last message, the flag will be reset before handling the new message.
    This depends on radio config and build settings.
2026-05-01 Add parameter to Horn constructor for different HW configurations
2026-05-08 FIX: Button 4/5 were handled two times
2026-05-09 Restructuring of Controller Code
    WIP
    Introduced ShotClockLogic class
2026-05-10 Restructuring of Controller Code
    WIP
    platformio.ini:
    - removed lib_deps to heltec dev-boards
    Moved display functions to ShotClockUI
    - integrated setDataDisplay, setPauseDisplay, honk
    - added new telemetry data UI with ID, Battery and RSSI
2026-05-15 Added new Link Layer classes:
    - SCLink
    - ControllerLink
    - DisplayLink
    WIP
2026-05-16 Created DisplayLogic
    Introduced Interface classes for interaction between layers
    WIP
2026-05-17 Implemented RSSI and Battery voltage in telemetry data
    Implemented basic ID assignment
    Add confirmed devices to list
    SCLink:
    - added getRSSI()
    - added priority flag to protocol_t to insert in front of list
    - added some more logic to the state machine
2026-05-17 SCLink, ControllerLink, DisplayLink
    - use protocol_t for data transfer in functions
    - show ID after setID command
    ShotClockLogic:
    - fixed timings in pause mode
    - changed handling of telemetry command and response
    LEDs:

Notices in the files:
parts and their libraries:
SparkFun-Switches: Licensing: Creative Commons ShareAlike 4.0 International - https://creativecommons.org/licenses/by-sa/4.0
